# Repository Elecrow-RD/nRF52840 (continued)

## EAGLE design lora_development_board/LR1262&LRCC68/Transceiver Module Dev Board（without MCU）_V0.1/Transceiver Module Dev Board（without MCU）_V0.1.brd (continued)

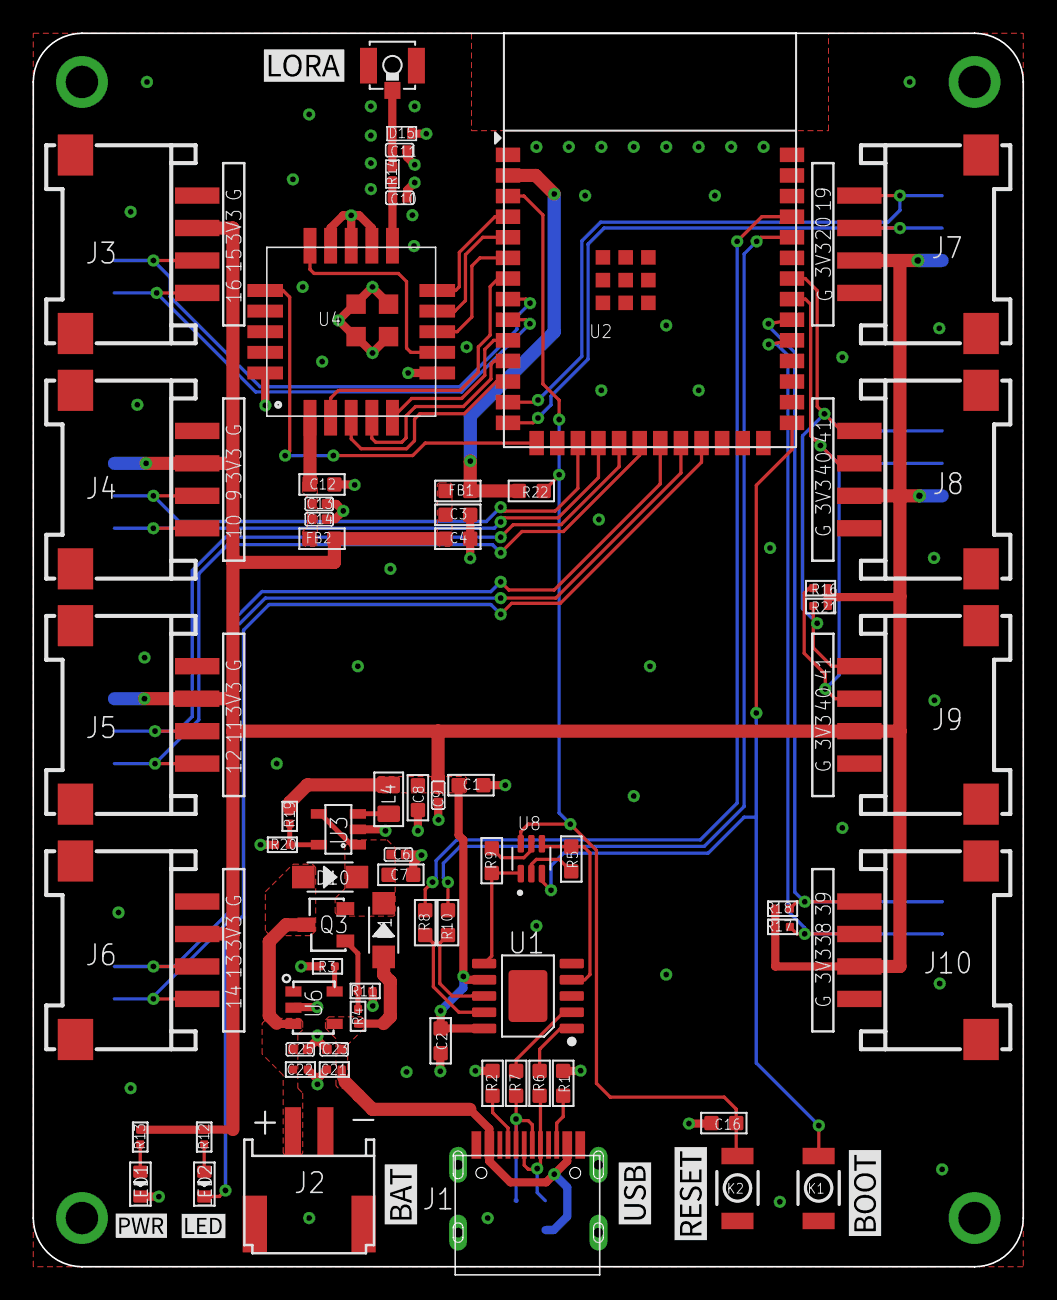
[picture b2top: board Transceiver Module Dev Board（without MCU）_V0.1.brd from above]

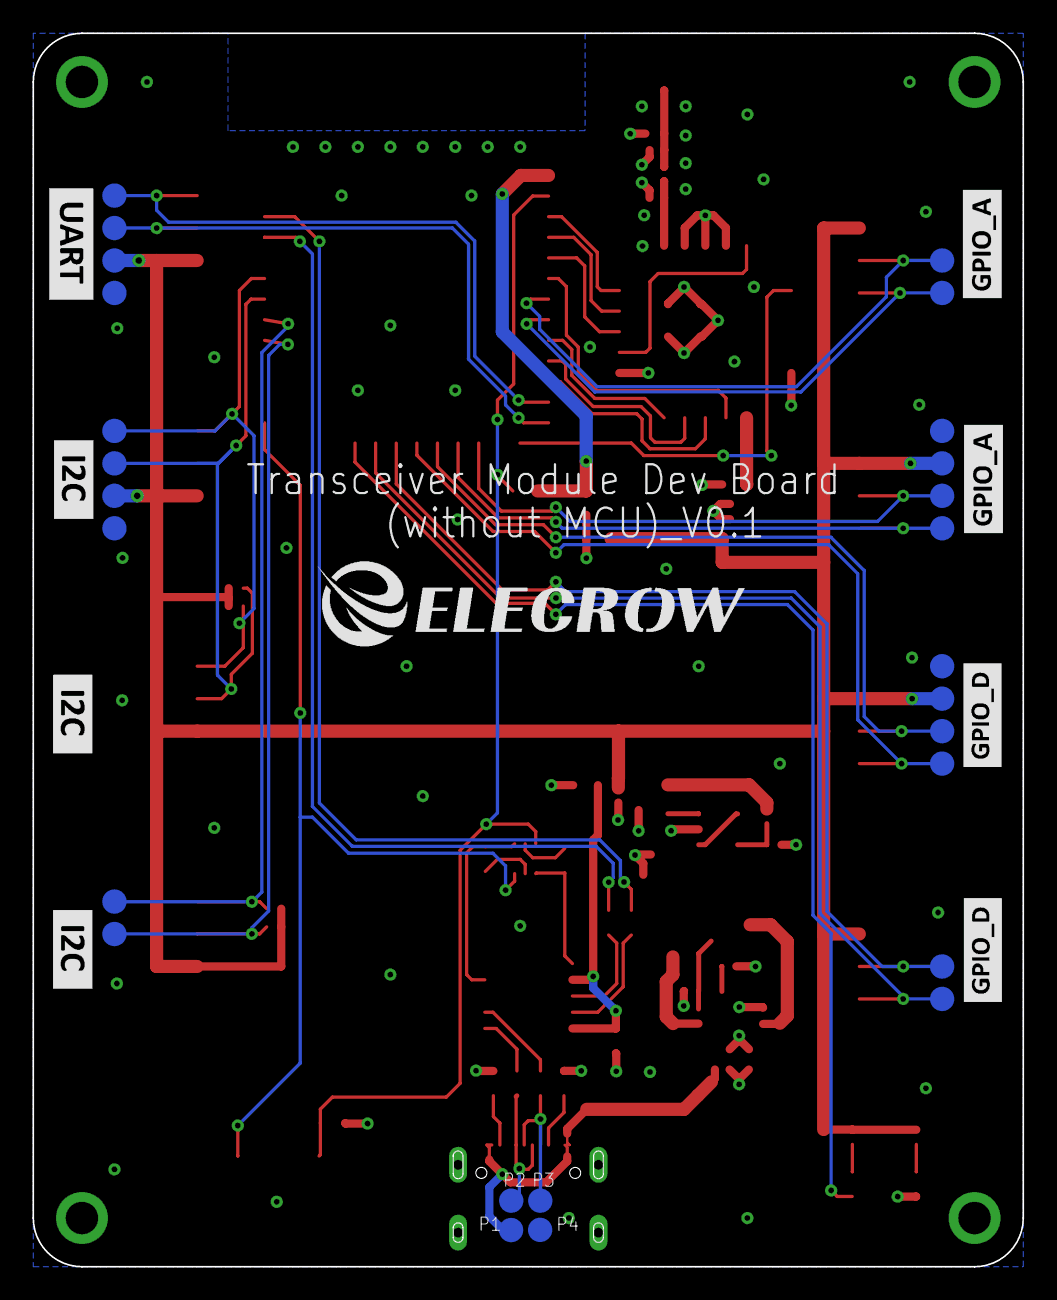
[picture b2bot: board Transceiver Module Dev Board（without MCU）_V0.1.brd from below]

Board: 2 copper layers, 61.0 x 76.0 mm, 93 parts (26 on the bottom side), 55 nets.
